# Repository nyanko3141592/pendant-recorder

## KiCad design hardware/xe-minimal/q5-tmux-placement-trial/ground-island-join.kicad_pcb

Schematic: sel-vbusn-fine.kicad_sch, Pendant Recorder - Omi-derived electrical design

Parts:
C1, C2, C3, C6, C9, C22, C26: 100n; C_0402_1005Metric
C4: 10u; C_0603_1608Metric
C5: 4.7u; C_0603_1608Metric
C7, C16, C25: 1u; C_0402_1005Metric
C13: 2.2u 10V; C_0402_1005Metric
C14: 2.2u; C_0402_1005Metric
C15: 10u 10V effective >=1u; C_0603_1608Metric
C27: 4.7u effective TBD; C_0603_1608Metric
C28: 10n; C_0402_1005Metric
C29, C32, C33: 100n 10V; C_0402_1005Metric
C30: 50p 50V C0G; C_0402_1005Metric
C31: 1u 10V; C_0402_1005Metric
C34: 100n 10V candidate; C_0402_1005Metric
D6: amber LED 0402 TBD; LED_0402_1005Metric
J1: USB4105-GF-A (candidate); USB_C_GCT_USB4105_GroundLand112
J2: Molex781710003 / DTP401525-XE; Molex_Pico-EZmate_78171-0003_1x03-1MP_P1.20mm_Vertical
J3: Factory SWD pogo candidate; SWD_Pogo_5Pad_P1.27mm
Q3, Q4: DMN63D8L-7; SOT-23
Q6, Q7: 2N7002; SOT-23
R1: 0R; R_0402_1005Metric
R2: 10k; R_0402_1005Metric
R3, R4, R13, R15, R22: 100k; R_0402_1005Metric
R6, R7: 5.1k 1%; R_0402_1005Metric
R10: 6.8k 1%; R_0402_1005Metric
R11, R39: 20k 1%; R_0402_1005Metric
R12, R36, R37, R38, R40, R45, R46, R49, R50: 100k 1%; R_0402_1005Metric
R14: 1M; R_0402_1005Metric
R21, R23: 22R tentative; R_0402_1005Metric
R24, R25, R28: 47k; R_0402_1005Metric
R32: 6.8k tentative; R_0402_1005Metric
R33, R34: 1M 1%; R_0402_1005Metric
R35, R47, R48: 10k 1%; R_0402_1005Metric
R41: 7.5k 1%; R_0402_1005Metric
R42: 130k 1%; R_0402_1005Metric
R43: 4.7k 1%; R_0402_1005Metric
R44: 390k 1%; R_0402_1005Metric
SW1: B3U-1000P (candidate); SW_SPST_B3U-1000P
TH1: NCP18XH103F03RB 10k 1% B3380 candidate; R_0603_1608Metric
TP1, TP2, TP3, TP5, TP6: TestPoint; TestPoint_Pad_D1.0mm
U1: STM32U535CEU6; QFN-48-1EP_7x7mm_P0.5mm_EP5.6x5.6mm
U2: USBLC6-2P6; SOT-666
U3: BQ25185DLHR; Texas_DLH0010A_WSON-10-1EP_2.2x2mm_P0.4mm_EP0.9x1.5mm
U4: TPS7A0233PDBVR; SOT-23-5
U8: IM69D130V01XTSA1; IM69D130_JLC_SMD_trial
U10: TPS22916CYFPR; TPS22916_YFP4
U11: CSNP32GCR01-BOW candidate; CSNP32GCR01_LGA8
U12: TLV7042DDFR; SOT-23-8
U13: MAX4995CAUT+T; SOT-23-6
U14: SN74HCS74DYYR; Texas_DYY0014A
U15: TLV803EB29DBZR; SOT-23
U16: TMUX1101DCKR candidate; SOT-353_SC-70-5

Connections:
/BAT: C14.1, J2.1 (PACK_PLUS), R33.1, TP1.1, U3.2 (BAT)
/BAT_ADC: C28.1, R33.2, R34.1, U1.11 (PA1)
/BAT_TS: R37.2, TH1.1 (SENSE), U12.2 (INA-), U12.5 (INB+)
/BOOT0: R3.1, U1.44 (PH3)
/BUTTON_N: R4.2, SW1.1, U1.38 (PA15)
/CC1: J1.A5 (CC1), R6.1
/CC2: J1.B5 (CC2), R7.1
/CHARGER_TS: R35.1, U3.6 (TS_MR)
/CHG_ALLOW: R43.1, U1.20 (PB2)
/CHG_GUARD_GATE: Q4.1 (G), R36.1, R43.2, U12.1 (OUTA), U12.7 (OUTB)
/CHG_INHIBIT_GATE: Q4.3 (D), R12.2, U3.4 (CE_N)
/CHG_N: R11.2, U1.27 (PB14), U3.9 (STAT1)
/GND: C1.2, C2.2, C3.2, C4.2, C5.2, C6.2, C7.2, C9.2, C13.2, C14.2, C15.2, C16.2, C22.2, C25.2, C26.2, C27.2, C28.2, C29.2, C30.2, C31.2, C32.2, C33.2, C34.2, D6.1 (K), J1.A1 (GND), J1.A12 (GND), J1.B1 (GND), J1.B12 (GND), J1.SH (SHIELD), J2.3 (PACK_MINUS), J3.5 (GND), Q3.2 (S), Q4.2 (S), Q6.2 (S), Q7.2 (S), R3.2, R6.2, R7.2, R10.2, R14.2, R22.2, R34.2, R35.2, R36.2, R39.2, R41.2, R42.2, R44.2, R46.2, R49.2, R50.2, SW1.2, TH1.2 (RETURN), TP6.1, U1.8 (VSSA), U1.23 (VSS), U1.35 (VSS), U1.47 (VSS), U1.49 (VSS), U2.2 (GND), U3.5 (GND), U3.11 (EP), U4.2 (GND), U8.4 (SELECT), U8.5 (GND), U10.B1 (GND), U11.4 (VSS), U12.4 (VEE), U13.2 (GND), U14.7 (GND), U14.11 (2CLK), U14.12 (2D), U14.13 (2CLR_N), U15.1 (GND), U16.2 (S), U16.3 (GND)
/ILIM_VSET: R42.1, U3.7 (ILIM_VSET)
/ISET: C30.1, R10.1, U3.8 (ISET)
/NRST: C9.1, J3.3 (nRESET), R2.2, U1.7 (NRST)
/PDM_CLK: R21.2, U8.3 (CLOCK)
/PDM_CLK_MCU: R21.1, U1.39 (PB3)
/PDM_DATA: U1.40 (PB4), U8.1 (DATA)
/SD_CLK: R23.2, U11.3 (CLK)
/SD_CLK_MCU: R23.1, U1.15 (PA5)
/SD_CS_N: R28.2, U1.14 (PA4), U11.2 (CS_N)
/SD_EN: R22.1, U1.41 (PB5), U10.B2 (ON)
/SD_MISO: R25.2, U1.16 (PA6), U11.6 (DO)
/SD_MOSI: R24.2, U1.17 (PA7), U11.5 (DI)
/SD_V3: C26.1, C27.1, R24.1, R25.1, R28.1, TP5.1, U10.A1 (VOUT), U11.8 (VDD)
/STATUS_LED: R32.1, U1.29 (PA8)
/STATUS_LED_A: D6.2 (A), R32.2
/SWCLK: J3.4 (SWCLK), U1.37 (PA14)
/SWDIO: J3.2 (SWDIO), U1.34 (PA13)
/SYS: C15.1, TP2.1, U3.1 (SYS), U4.1 (IN), U4.3 (EN)
/TS_COLD_REF: R38.2, R39.1, U12.3 (INA+)
/TS_HOT_REF: R40.2, R41.1, U12.6 (INB-)
/USB_DM: J1.A7 (D-), J1.B7 (D-), U1.32 (PA11), U2.3 (IO2), U2.4 (IO2)
/USB_DP: J1.A6 (D+), J1.B6 (D+), U1.33 (PA12), U2.1 (IO1), U2.6 (IO1)
/USB_HIGH_BUDGET: R46.1, U1.42 (PB6), U16.4 (SEL)
/USB_HIGH_BUDGET_DRAIN: R45.2, U16.1 (D)
/USB_ILIM_SET: R44.1, R45.1, U13.3 (SETI)
/USB_INPUT_ON: U13.4 (ON), U14.6 (1Q_N)
/USB_LATCH_CLEAR_N: Q7.3 (D), R48.2, U14.1 (1CLR_N), U15.2 (RESET_N)
/USB_LATCH_CLOCK: Q6.3 (D), R47.2, U14.3 (1CLK)
/USB_RESUME_PULSE: Q7.1 (G), R50.1, U1.19 (PB1)
/USB_SUSPEND_PULSE: Q6.1 (G), R49.1, U1.12 (PA2)
/V3V3: C1.1, C2.1, C3.1, C4.1, C16.1, C22.1, C25.1, C29.1, J3.1 (VTref), R1.1, R2.1, R4.1, R11.1, R15.1, R37.1, R38.1, R40.1, TP3.1, U1.1 (VBAT), U1.24 (VDD), U1.36 (VDD), U1.48 (VDD), U4.5 (OUT), U8.2 (VDD), U10.A2 (VIN), U12.8 (VCC)
/VBUS: C31.1, C32.1, C33.1, C34.1, J1.A4 (VBUS), J1.A9 (VBUS), J1.B4 (VBUS), J1.B9 (VBUS), R13.1, R47.1, R48.1, U2.5 (VBUS), U13.5 (IN), U14.2 (1D), U14.4 (1PRE_N), U14.10 (2PRE_N), U14.14 (VCC), U15.3 (VDD), U16.5 (VDD)
/VBUS_GATE: Q3.1 (G), R13.2, R14.1
/VBUS_LIMITED: C13.1, R12.1, U3.10 (IN), U13.1 (OUT)
/VBUS_N: Q3.3 (D), R15.2, U1.10 (PA0)
/VCAP: C5.1, U1.22 (VCAP)
/VDDA: C6.1, C7.1, R1.2, U1.9 (VDDA)

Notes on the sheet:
01 MCU / RTC / UI
02 USB-C / CHARGER
03 POWER / FUEL GAUGE
04 AUDIO / SD / INDICATORS
ENGINEERING DRAFT - NOT FOR FABRICATION - See hardware/xe-minimal/README.md

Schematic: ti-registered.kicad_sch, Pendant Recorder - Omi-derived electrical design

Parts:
C1, C2, C3, C6, C9, C22, C26: 100n; C_0402_1005Metric
C4: 10u; C_0603_1608Metric
C5: 4.7u; C_0603_1608Metric
C7, C16, C25: 1u; C_0402_1005Metric
C13: 2.2u 10V; C_0402_1005Metric
C14: 2.2u; C_0402_1005Metric
C15: 10u 10V effective >=1u; C_0603_1608Metric
C27: 4.7u effective TBD; C_0603_1608Metric
C28: 10n; C_0402_1005Metric
C29, C32, C33: 100n 10V; C_0402_1005Metric
C30: 50p 50V C0G; C_0402_1005Metric
C31: 1u 10V; C_0402_1005Metric
C34: 100n 10V candidate; C_0402_1005Metric
D6: amber LED 0402 TBD; LED_0402_1005Metric
J1: USB4105-GF-A (candidate); USB_C_GCT_USB4105_GroundLand112
J2: Molex781710003 / DTP401525-XE; Molex_Pico-EZmate_78171-0003_1x03-1MP_P1.20mm_Vertical
J3: Factory SWD pogo candidate; SWD_Pogo_5Pad_P1.27mm
Q3, Q4: DMN63D8L-7; SOT-23
Q6, Q7: 2N7002; SOT-23
R1: 0R; R_0402_1005Metric
R2: 10k; R_0402_1005Metric
R3, R4, R13, R15, R22: 100k; R_0402_1005Metric
R6, R7: 5.1k 1%; R_0402_1005Metric
R10: 6.8k 1%; R_0402_1005Metric
R11, R39: 20k 1%; R_0402_1005Metric
R12, R36, R37, R38, R40, R45, R46, R49, R50: 100k 1%; R_0402_1005Metric
R14: 1M; R_0402_1005Metric
R21, R23: 22R tentative; R_0402_1005Metric
R24, R25, R28: 47k; R_0402_1005Metric
R32: 6.8k tentative; R_0402_1005Metric
R33, R34: 1M 1%; R_0402_1005Metric
R35, R47, R48: 10k 1%; R_0402_1005Metric
R41: 7.5k 1%; R_0402_1005Metric
R42: 130k 1%; R_0402_1005Metric
R43: 4.7k 1%; R_0402_1005Metric
R44: 390k 1%; R_0402_1005Metric
SW1: B3U-1000P (candidate); SW_SPST_B3U-1000P
TH1: NCP18XH103F03RB 10k 1% B3380 candidate; R_0603_1608Metric
TP1, TP2, TP3, TP5, TP6: TestPoint; TestPoint_Pad_D1.0mm
U1: STM32U535CEU6; QFN-48-1EP_7x7mm_P0.5mm_EP5.6x5.6mm
U2: USBLC6-2P6; SOT-666
U3: BQ25185DLHR; Texas_DLH0010A_WSON-10-1EP_2.2x2mm_P0.4mm_EP0.9x1.5mm
U4: TPS7A0233PDBVR; SOT-23-5
U8: IM69D130V01XTSA1; IM69D130_JLC_SMD_trial
U10: TPS22916CYFPR; TPS22916_YFP4
U11: CSNP32GCR01-BOW candidate; CSNP32GCR01_LGA8
U12: TLV7042DDFR; SOT-23-8
U13: MAX4995CAUT+T; SOT-23-6
U14: SN74HCS74DYYR; Texas_DYY0014A
U15: TLV803EB29DBZR; SOT-23
U16: TMUX1101DCKR candidate; TMUX1101_DCK0005A_TI_4214834G

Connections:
/BAT: C14.1, J2.1 (PACK_PLUS), R33.1, TP1.1, U3.2 (BAT)
/BAT_ADC: C28.1, R33.2, R34.1, U1.11 (PA1)
/BAT_TS: R37.2, TH1.1 (SENSE), U12.2 (INA-), U12.5 (INB+)
/BOOT0: R3.1, U1.44 (PH3)
/BUTTON_N: R4.2, SW1.1, U1.38 (PA15)
/CC1: J1.A5 (CC1), R6.1
/CC2: J1.B5 (CC2), R7.1
/CHARGER_TS: R35.1, U3.6 (TS_MR)
/CHG_ALLOW: R43.1, U1.20 (PB2)
/CHG_GUARD_GATE: Q4.1 (G), R36.1, R43.2, U12.1 (OUTA), U12.7 (OUTB)
/CHG_INHIBIT_GATE: Q4.3 (D), R12.2, U3.4 (CE_N)
/CHG_N: R11.2, U1.27 (PB14), U3.9 (STAT1)
/GND: C1.2, C2.2, C3.2, C4.2, C5.2, C6.2, C7.2, C9.2, C13.2, C14.2, C15.2, C16.2, C22.2, C25.2, C26.2, C27.2, C28.2, C29.2, C30.2, C31.2, C32.2, C33.2, C34.2, D6.1 (K), J1.A1 (GND), J1.A12 (GND), J1.B1 (GND), J1.B12 (GND), J1.SH (SHIELD), J2.3 (PACK_MINUS), J3.5 (GND), Q3.2 (S), Q4.2 (S), Q6.2 (S), Q7.2 (S), R3.2, R6.2, R7.2, R10.2, R14.2, R22.2, R34.2, R35.2, R36.2, R39.2, R41.2, R42.2, R44.2, R46.2, R49.2, R50.2, SW1.2, TH1.2 (RETURN), TP6.1, U1.8 (VSSA), U1.23 (VSS), U1.35 (VSS), U1.47 (VSS), U1.49 (VSS), U2.2 (GND), U3.5 (GND), U3.11 (EP), U4.2 (GND), U8.4 (SELECT), U8.5 (GND), U10.B1 (GND), U11.4 (VSS), U12.4 (VEE), U13.2 (GND), U14.7 (GND), U14.11 (2CLK), U14.12 (2D), U14.13 (2CLR_N), U15.1 (GND), U16.2 (S), U16.3 (GND)
/ILIM_VSET: R42.1, U3.7 (ILIM_VSET)
/ISET: C30.1, R10.1, U3.8 (ISET)
/NRST: C9.1, J3.3 (nRESET), R2.2, U1.7 (NRST)
/PDM_CLK: R21.2, U8.3 (CLOCK)
/PDM_CLK_MCU: R21.1, U1.39 (PB3)
/PDM_DATA: U1.40 (PB4), U8.1 (DATA)
/SD_CLK: R23.2, U11.3 (CLK)
/SD_CLK_MCU: R23.1, U1.15 (PA5)
/SD_CS_N: R28.2, U1.14 (PA4), U11.2 (CS_N)
/SD_EN: R22.1, U1.41 (PB5), U10.B2 (ON)
/SD_MISO: R25.2, U1.16 (PA6), U11.6 (DO)
/SD_MOSI: R24.2, U1.17 (PA7), U11.5 (DI)
/SD_V3: C26.1, C27.1, R24.1, R25.1, R28.1, TP5.1, U10.A1 (VOUT), U11.8 (VDD)
/STATUS_LED: R32.1, U1.29 (PA8)
/STATUS_LED_A: D6.2 (A), R32.2
/SWCLK: J3.4 (SWCLK), U1.37 (PA14)
/SWDIO: J3.2 (SWDIO), U1.34 (PA13)
/SYS: C15.1, TP2.1, U3.1 (SYS), U4.1 (IN), U4.3 (EN)
/TS_COLD_REF: R38.2, R39.1, U12.3 (INA+)
/TS_HOT_REF: R40.2, R41.1, U12.6 (INB-)
/USB_DM: J1.A7 (D-), J1.B7 (D-), U1.32 (PA11), U2.3 (IO2), U2.4 (IO2)
/USB_DP: J1.A6 (D+), J1.B6 (D+), U1.33 (PA12), U2.1 (IO1), U2.6 (IO1)
/USB_HIGH_BUDGET: R46.1, U1.42 (PB6), U16.4 (SEL)
/USB_HIGH_BUDGET_DRAIN: R45.2, U16.1 (D)
/USB_ILIM_SET: R44.1, R45.1, U13.3 (SETI)
/USB_INPUT_ON: U13.4 (ON), U14.6 (1Q_N)
/USB_LATCH_CLEAR_N: Q7.3 (D), R48.2, U14.1 (1CLR_N), U15.2 (RESET_N)
/USB_LATCH_CLOCK: Q6.3 (D), R47.2, U14.3 (1CLK)
/USB_RESUME_PULSE: Q7.1 (G), R50.1, U1.19 (PB1)
/USB_SUSPEND_PULSE: Q6.1 (G), R49.1, U1.12 (PA2)
/V3V3: C1.1, C2.1, C3.1, C4.1, C16.1, C22.1, C25.1, C29.1, J3.1 (VTref), R1.1, R2.1, R4.1, R11.1, R15.1, R37.1, R38.1, R40.1, TP3.1, U1.1 (VBAT), U1.24 (VDD), U1.36 (VDD), U1.48 (VDD), U4.5 (OUT), U8.2 (VDD), U10.A2 (VIN), U12.8 (VCC)
/VBUS: C31.1, C32.1, C33.1, C34.1, J1.A4 (VBUS), J1.A9 (VBUS), J1.B4 (VBUS), J1.B9 (VBUS), R13.1, R47.1, R48.1, U2.5 (VBUS), U13.5 (IN), U14.2 (1D), U14.4 (1PRE_N), U14.10 (2PRE_N), U14.14 (VCC), U15.3 (VDD), U16.5 (VDD)
/VBUS_GATE: Q3.1 (G), R13.2, R14.1
/VBUS_LIMITED: C13.1, R12.1, U3.10 (IN), U13.1 (OUT)
/VBUS_N: Q3.3 (D), R15.2, U1.10 (PA0)
/VCAP: C5.1, U1.22 (VCAP)
/VDDA: C6.1, C7.1, R1.2, U1.9 (VDDA)

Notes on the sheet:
01 MCU / RTC / UI
02 USB-C / CHARGER
03 POWER / FUEL GAUGE
04 AUDIO / SD / INDICATORS
ENGINEERING DRAFT - NOT FOR FABRICATION - See hardware/xe-minimal/README.md

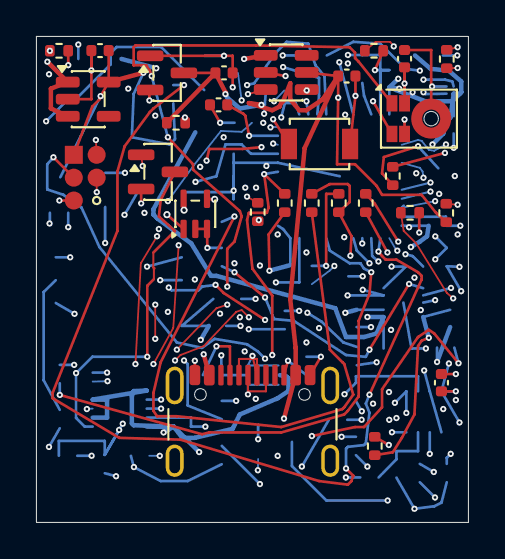
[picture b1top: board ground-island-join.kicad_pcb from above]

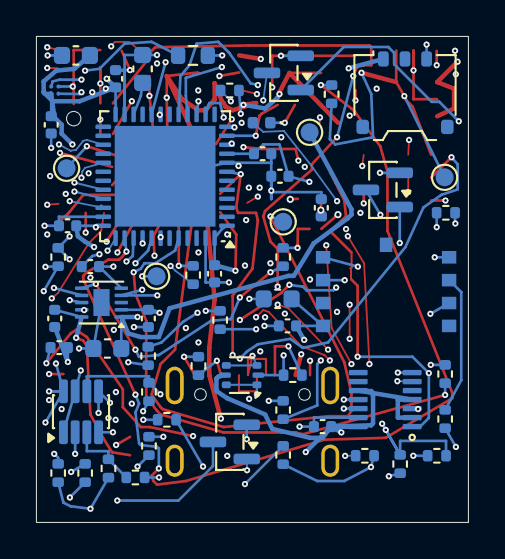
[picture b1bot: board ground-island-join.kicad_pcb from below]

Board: 6 copper layers, 24.0 x 27.0 mm, 87 parts (59 on the bottom side), 50 nets.

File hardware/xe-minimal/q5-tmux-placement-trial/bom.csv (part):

Reference,Part/value,Footprint,Design note
U1,STM32U535CEU6,Package_DFN_QFN:QFN-48-1EP_7x7mm_P0.5mm_EP5.6x5.6mm,512KB Flash/274KB RAM; non-SMPS UFQFPN48. PB3/PB4 ADF AF3; PA5/6/7 SPI1 AF5. VDD USB shared 3.3V. JLC acceptance and pin review pending.
C1,100n,Capacitor_SMD:C_0402_1005Metric,
C4,10u,Capacitor_SMD:C_0603_1608Metric,Main bulk capacitor; check startup and effective capacitance.
C9,100n,Capacitor_SMD:C_0402_1005Metric,
R2,10k,Resistor_SMD:R_0402_1005Metric,
J3,Factory SWD pogo candidate,PendantMinimal:SWD_Pogo_5Pad_P1.27mm,Five exposed pads; factory fixture required; VTref sense only. No buyer flashing.
SW1,B3U-1000P (candidate),Button_Switch_SMD:SW_SPST_B3U-1000P,
R4,100k,Resistor_SMD:R_0402_1005Metric,
J1,USB4105-GF-A (candidate),PendantD1:USB_C_GCT_USB4105_GroundLand112,Exact footprint and shield pad numbering pending connector selection
R6,5.1k 1%,Resistor_SMD:R_0402_1005Metric,
R7,5.1k 1%,Resistor_SMD:R_0402_1005Metric,
U2,USBLC6-2P6,Package_TO_SOT_SMD:SOT-666,"ST DS4260 same 6-pin function diagram; smaller package, LCSC C15999 catalog; orientation/land pattern final audit pending."
C13,2.2u 10V,Capacitor_SMD:C_0402_1005Metric,
U3,BQ25185DLHR,Package_DFN_QFN:Texas_DLH0010A_WSON-10-1EP_2.2x2mm_P0.4mm_EP0.9x1.5mm,XE candidate4.1V ±0.5% =>4.1205V upper;44.12mA nominal charging. ILIM500 requires host power policy; thermal contact and battery capacity at4.1V unqualified; charge inhibited.
R10,6.8k 1%,Resistor_SMD:R_0402_1005Metric,XE prototype44.12mA nominal;10%IC/1%R screen39.31..49.02mA below110mA pack maximum. Nominal4.41mA termination exceeds manufacturer1.1mA reference; capacity/16h not guaranteed. No charge enable.
R11,20k 1%,Resistor_SMD:R_0402_1005Metric,
C14,2.2u,Capacitor_SMD:C_0402_1005Metric,
J2,Molex781710003 / DTP401525-XE,Connector_Molex:Molex_Pico-EZmate_78171-0003_1x03-1MP_P1.20mm_Vertical,"Pack manufacturer p9:1red+,2NTC,3black-. Header mating-view pad alignment still requires validation. Built-in NTC has no identified R-T curve; pin2 deliberately NC. Independent factory-mountedTH1 contact sensor is mandatory; no user soldering. Reverse polarity protection review pending."
R12,100k 1%,Resistor_SMD:R_0402_1005Metric,"YAGEO RC0402FR-07100KL; 100k 1%, +/-100ppm/C. Pulls U3 CE high from VBUS_LIMITED to inhibit charging when Q4 is off; no Q2 in this path."
C15,10u 10V effective >=1u,Capacitor_SMD:C_0603_1608Metric,SYS cap per TI; DC-bias capacitance must be qualified.
U4,TPS7A0233PDBVR,Package_TO_SOT_SMD:SOT-23-5,3.3V main rail: 48-pin MCU has no separate USB supply; dropout/capacity measurement required.
C16,1u,Capacitor_SMD:C_0402_1005Metric,
U8,IM69D130V01XTSA1,Pendant:IM69D130_JLC_SMD_trial,"Direct 3.3V PDM, bottom port; no AAD. 0.768MHz/decimation48 candidate for 16kHz; acoustic validation required."
R21,22R tentative,Resistor_SMD:R_0402_1005Metric,
C22,100n,Capacitor_SMD:C_0402_1005Metric,
U10,TPS22916CYFPR,Pendant:TPS22916_YFP4,Omi SD switch; power-off sequence must tristate ALL SD signals
R22,100k,Resistor_SMD:R_0402_1005Metric,
C25,1u,Capacitor_SMD:C_0402_1005Metric,
R23,22R tentative,Resistor_SMD:R_0402_1005Metric,
R24,47k,Resistor_SMD:R_0402_1005Metric,
R25,47k,Resistor_SMD:R_0402_1005Metric,
R28,47k,Resistor_SMD:R_0402_1005Metric,
C26,100n,Capacitor_SMD:C_0402_1005Metric,
C27,4.7u effective TBD,Capacitor_SMD:C_0603_1608Metric,
TP1,TestPoint,TestPoint:TestPoint_Pad_D1.0mm,
TP2,TestPoint,TestPoint:TestPoint_Pad_D1.0mm,
TP3,TestPoint,TestPoint:TestPoint_Pad_D1.0mm,
TP5,TestPoint,TestPoint:TestPoint_Pad_D1.0mm,
TP6,TestPoint,TestPoint:TestPoint_Pad_D1.0mm,
R32,6.8k tentative,Resistor_SMD:R_0402_1005Metric,"LED current target 0.1-0.2mA; verify LED Vf, daylight readability and GPIO limits"
D6,amber LED 0402 TBD,LED_SMD:LED_0402_1005Metric,"Single status/battery indicator; firmware blinks on demand, normally dark."
C2,100n,Capacitor_SMD:C_0402_1005Metric,
C3,100n,Capacitor_SMD:C_0402_1005Metric,
C5,4.7u,Capacitor_SMD:C_0603_1608Metric,
C6,100n,Capacitor_SMD:C_0402_1005Metric,
C7,1u,Capacitor_SMD:C_0402_1005Metric,
R1,0R,Resistor_SMD:R_0402_1005Metric,
R3,100k,Resistor_SMD:R_0402_1005Metric,
Q3,DMN63D8L-7,Package_TO_SOT_SMD:SOT-23,"Diodes DMN63D8L-7 selected for engineering prototype VBUS presence detection; pin1 G pin2 S pin3 D. Temperature, detection and solder process qualification pending."
R13,100k,Resistor_SMD:R_0402_1005Metric,Purchase specification: YAGEO RC0402FR-07100KL; 0402; 1%; +/-100 ppm/C; 0.063 W at 70 C; 50 V working limit. Supplier SKU/price and circuit qualification pending.
R14,1M,Resistor_SMD:R_0402_1005Metric,Purchase specification: YAGEO RC0402FR-071ML; 0402; 1%; +/-100 ppm/C; 0.063 W at 70 C; 50 V working limit. Supplier SKU/price and circuit qualification pending.
R15,100k,Resistor_SMD:R_0402_1005Metric,Purchase specification: YAGEO RC0402FR-07100KL; 0402; 1%; +/-100 ppm/C; 0.063 W at 70 C; 50 V working limit. Supplier SKU/price and circuit qualification pending.
R33,1M 1%,Resistor_SMD:R_0402_1005Metric,"Battery divider 1:2; sample after settling, calibrate with VREFINT; not coulomb counting."
R34,1M 1%,Resistor_SMD:R_0402_1005Metric,"Battery divider 1:2; sample after settling, calibrate with VREFINT; not coulomb counting."
C28,10n,Capacitor_SMD:C_0402_1005Metric,"Battery divider 1:2; sample after settling, calibrate with VREFINT; not coulomb counting."
R35,10k 1%,Resistor_SMD:R_0402_1005Metric,Holds normal TS level when released; no floating TS/TTDM in intended circuit.
R36,100k 1%,Resistor_SMD:R_0402_1005Metric,"YAGEO RC0402FR-07100KL; 100k 1%, +/-100ppm/C. Reset/high-Z gate pulldown; no charging permission."
R37,100k 1%,Resistor_SMD:R_0402_1005Metric,Reduce thermistor excitation; 5.25V and99k gives52.99uA maximum branch current and69.60uW maximum thermistor power. Only powered from USB. Shared MCU rail for USB-independent temperature guard; BOR4 and startup timing qualification required.
R38,100k 1%,Resistor_SMD:R_0402_1005Metric, Shared MCU rail for USB-independent temperature guard; BOR4 and startup timing qualification required.
R39,20k 1%,Resistor_SMD:R_0402_1005Metric,Cold threshold candidate. Beta-model sensitivity is not full manufacturer R-T qualification. See temperature-screen.json.
R40,100k 1%,Resistor_SMD:R_0402_1005Metric, Shared MCU rail for USB-independent temperature guard; BOR4 and startup timing qualification required.
R41,7.5k 1%,Resistor_SMD:R_0402_1005Metric,Hot threshold candidate. Reserve margin for contact sensor lag; physical thermal qualification required.
U12,TLV7042DDFR,Package_TO_SOT_SMD:SOT-23-8,"Open-drain wired-AND temperature permission. Either fault pulls Q4 gate low. Board NTC replaces undocumented pack NTC; exact R-T, common-mode error and thermal contact not qualified. Shared MCU rail for USB-independent temperature guard; BOR4 and startup timing qualification required."
Q4,DMN63D8L-7,Package_TO_SOT_SMD:SOT-23,Diodes DMN63D8L-7 engineering prototype; pulls charger CE low only with permission and both temperature comparators released. Off-current and thermal fault behavior require bench qualification.
C29,100n 10V,Capacitor_SMD:C_0402_1005Metric,Place adjacent to U12 supply pins. Shared MCU rail for USB-independent temperature guard; BOR4 and startup timing qualification required.
R42,130k 1%,Resistor_SMD:R_0402_1005Metric,BQ25185 Table6-1:4.1V / ILIM500. Input450/475/498mA. Requires USB preconfiguration/suspend power management; charge stays disabled pending qualification.
C30,50p 50V C0G,Capacitor_SMD:C_0402_1005Metric,BQ25185 SLUSF65B6.1.1.4 low-current <50mA recommendation; final transient behavior requires hardware test.
R43,4.7k 1%,Resistor_SMD:R_0402_1005Metric,"YAGEO RC0402FR-074K7L; 4.7k 1%, +/-100ppm/C, 0.063W at70C. Lowered from10k to improve Q4 gate drive; comparator fault clamp load screen0.724mA, not measured."
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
